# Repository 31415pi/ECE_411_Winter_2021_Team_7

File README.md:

# ECE411 Sunrise Alarm Clock - Team 7
,
> "Never wake-up in darkness..."

Actual project completion utilized a completely different set of hardware. Updates forthcoming. The Sunrise Alarm Clock is an add on board for an arduino which allows users to interact with an OLED display clock using guestures. The board features 12 RGB SMD LEDs which are used to display time in a meaningful way, indicate confirmation of guesture input, and provide an illuminated alarm experience. A buzzer along with two analog buttons are included to facilitate traditional inputs and alarms if necessary. 

View the [Product Design Specification](./Product%20Design%20Specification%20v1.pdf) for more information.

Look at the [Project Board](https://github.com/31415pi/ECE_411_Winter_2021_Team_7/projects/1).

Schematic located at [Hardware/Schematic](./Hardware/Schematic.pdf).

## Parts List

Parts list on [google drive](https://docs.google.com/spreadsheets/d/1yFu2dnekZCLbKxV9tUKsMTaaS4XpjHtpUTBXEi358RU/edit#gid=0). [Convert to Markdown](https://tabletomarkdown.com/convert-spreadsheet-to-markdown/).

| Part (datasheet link)                                                                                                                                  | Name                                                 | Type            | Notes                        | Datasheet                                                                                                                                                                                                                                                                                                  | Website                                                                                                    | Source                                                          | Price  |
| ------------------------------------------------------------------------------------------------------------------------------------------------------ | ---------------------------------------------------- | --------------- | ---------------------------- | ---------------------------------------------------------------------------------------------------------------------------------------------------------------------------------------------------------------------------------------------------------------------------------------------------------- | ---------------------------------------------------------------------------------------------------------- | --------------------------------------------------------------- | ------ |
| [HT16K33](https://github.com/31415pi/ECE_411_Winter_2021_Team_7/blob/main/Datasheets/HT16K33v120(LEDcontroller).pdf)                                   | RAM Mapping 16\*8 LED Controller Driver with keyscan | LED Controller  |                              |                                                                                                                                                                                                                                                                                                            | [https://www.holtek.com/productdetail/-/vg/16K33](https://www.holtek.com/productdetail/-/vg/16K33)         |                                                                 |        |
| [PIC18F26K42](https://github.com/31415pi/ECE_411_Winter_2021_Team_7/blob/main/Datasheets/PIC18(L)F26-27-45-46-47-55-56-57K42-Data-Sheet-40001919G.pdf) |                                                      | Microcontroller | Actual Model Read from Chip. | [https://www.microchip.com/content/dam/mchp/documents/MCU08/ProductDocuments/DataSheets/PIC18(L)F26-27-45-46-47-55-56-57K42-Data-Sheet-40001919G.pdf](https://www.microchip.com/content/dam/mchp/documents/MCU08/ProductDocuments/DataSheets/PIC18(L)F26-27-45-46-47-55-56-57K42-Data-Sheet-40001919G.pdf) | [https://www.microchip.com/en-us/product/PIC18F26K42](https://www.microchip.com/en-us/product/PIC18F26K42) | EPL                                                             | $ 1.50 |
| [IRM-05-5](https://github.com/31415pi/ECE_411_Winter_2021_Team_7/blob/main/Datasheets/IRM-05(ac-5vsupply).pdf)                                         |                                                      | DC Power Supply |                              |                                                                                                                                                                                                                                                                                                            |                                                                                                            | [Mouser](https://www.mouser.com/ProductDetail/709-IRM05-5)      | $ 8.81 |
| [MOC3052TVM](https://github.com/31415pi/ECE_411_Winter_2021_Team_7/blob/main/Datasheets/MOC3052M(ACcont).pdf)                                          |                                                      | AC Controller   |                              |                                                                                                                                                                                                                                                                                                            |                                                                                                            | [Mouser](https://www.mouser.com/ProductDetail/512-MOC3052SR2M)  | $ 1.15 |
| [ACST410-8BTR](https://github.com/31415pi/ECE_411_Winter_2021_Team_7/blob/main/Datasheets/ACST410(ACswitch).pdf)                                       |                                                      | AC Switch       |                              |                                                                                                                                                                                                                                                                                                            |                                                                                                            | [Mouser](https://www.mouser.com/ProductDetail/511-ACST410-8BTR) | $ 0.85 |
| [SFH628A](https://github.com/31415pi/ECE_411_Winter_2021_Team_7/blob/main/Datasheets/SFH628A(ACsensor).pdf)                                            |                                                      | AC Sensor       |                              |                                                                                                                                                                                                                                                                                                            |                                                                                                            | [Mouser](https://www.mouser.com/ProductDetail/782-SFH6286-4T)   | $ 1.27 |
| [COM-10931](https://github.com/31415pi/ECE_411_Winter_2021_Team_7/blob/main/Datasheets/COM-10931_ATA3492BW(7seg4digitSparkfun).pdf)                    | 7-Segment Display - 4-Digit (White)                  | Time Display    |                              | [http://cdn.sparkfun.com/datasheets/Components/LED/ATA3492BW\_2.pdf](http://cdn.sparkfun.com/datasheets/Components/LED/ATA3492BW_2.pdf)                                                                                                                                                                    | [https://www.sparkfun.com/products/10931](https://www.sparkfun.com/products/10931)                         | [Mouser](https://www.mouser.com/ProductDetail/474-COM-10931)    | $ 2.63 |

Alternate [Sparkfun Time Display](https://www.sparkfun.com/products/10931).

## Tools

- KiCad. [Third Party Libraries](https://www.kicad.org/libraries/third_party/)
- [Library Loader](https://componentsearchengine.com/tools) for loading schematics into KiCad and others. [Setup Instructions](https://www.samacsys.com/kicad/)

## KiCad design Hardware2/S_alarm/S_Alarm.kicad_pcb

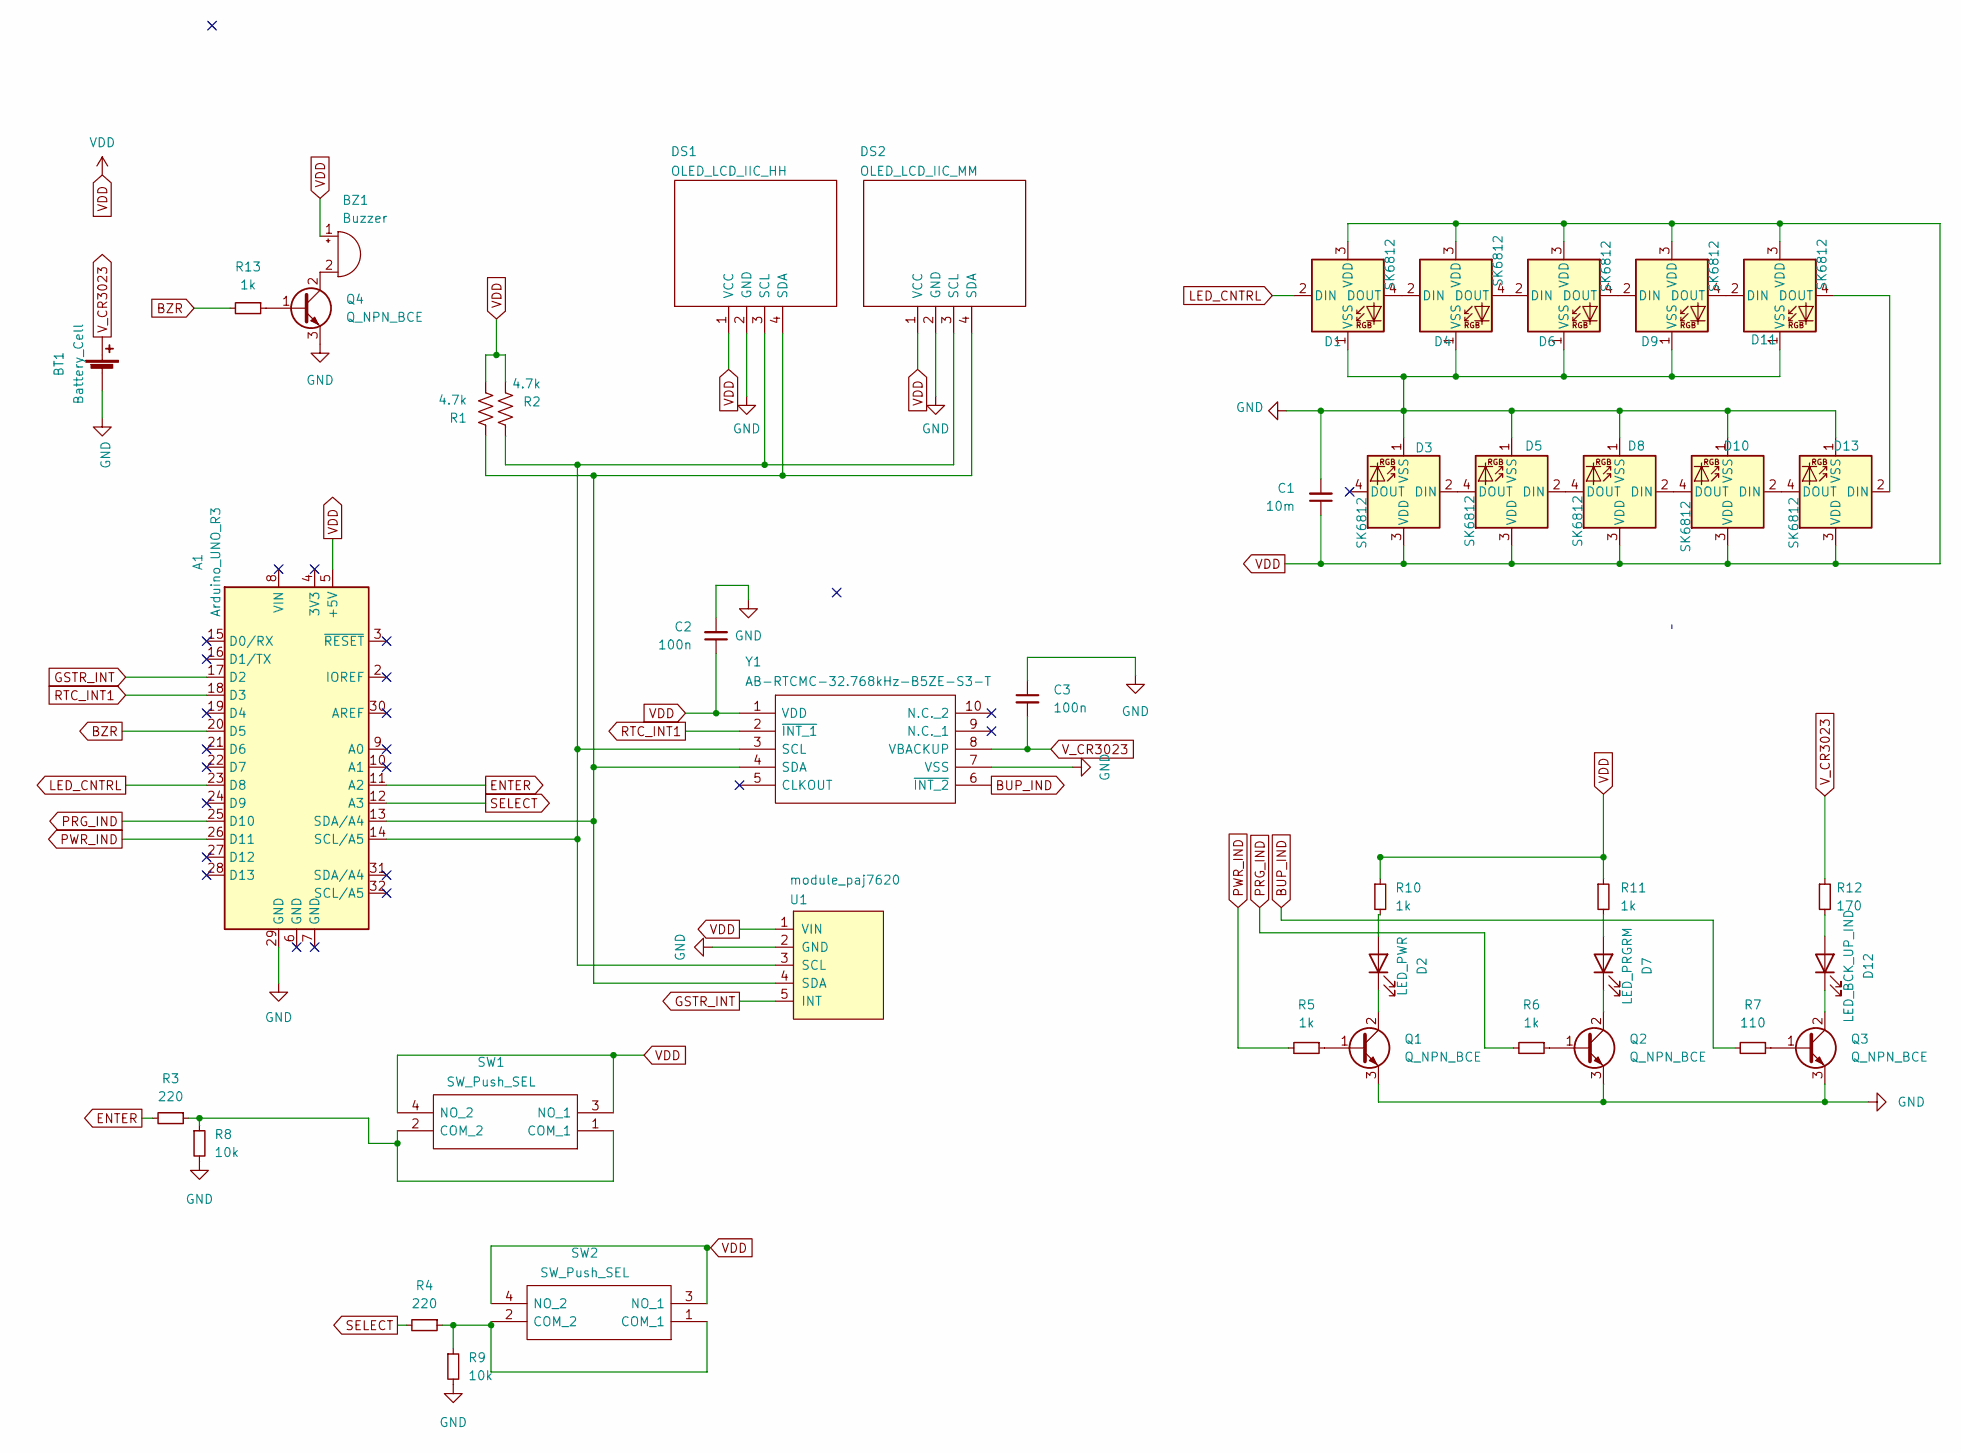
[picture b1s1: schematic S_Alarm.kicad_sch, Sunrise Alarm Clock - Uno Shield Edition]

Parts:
A1: Arduino_UNO_R3
BT1: Battery_Cell; BatteryHolder_MPD_BC2003_1x2032
BZ1: Buzzer; Buzzer_12x8.5RM6.5
C1: 10m; C_1206_3216Metric_Pad1.33x1.80mm_HandSolder
C2, C3: 100n; C_1206_3216Metric_Pad1.33x1.80mm_HandSolder
D1, D3, D4, D5, D6, D8, D9, D10, D11, D13: SK6812; LED_SK6812_PLCC4_5.0x5.0mm_P3.2mm
D2: LED_PWR; LED_1206_3216Metric_Pad1.42x1.75mm_HandSolder
D7: LED_PRGRM; LED_1206_3216Metric_Pad1.42x1.75mm_HandSolder
D12: LED_BCK_UP_IND; LED_1206_3216Metric_Pad1.42x1.75mm_HandSolder
DS1: OLED_LCD_IIC_HH; Display_OLED_128x64_0.96
DS2: OLED_LCD_IIC_MM; Display_OLED_128x64_0.96
Q1, Q2, Q3, Q4: Q_NPN_BCE; SOT-23_Handsoldering
R1, R2: 4.7k; R_1206_3216Metric_Pad1.30x1.75mm_HandSolder
R3, R4: 220; R_1206_3216Metric_Pad1.30x1.75mm_HandSolder
R5, R6, R10, R11, R13: 1k; R_1206_3216Metric_Pad1.30x1.75mm_HandSolder
R7: 110; R_1206_3216Metric_Pad1.30x1.75mm_HandSolder
R8, R9: 10k; R_1206_3216Metric_Pad1.30x1.75mm_HandSolder
R12: 170; R_1206_3216Metric_Pad1.30x1.75mm_HandSolder
SW1, SW2: SW_Push_SEL; PTS526SK15SMTR2LFS; Mouser Part Number 611-PTS526SK15SMR2L
U1: module_paj7620
Y1: AB-RTCMC-32.768kHz-B5ZE-S3-T; ABRTCMC32768kHzB5ZES3T; Manufacturer_Part_Number AB-RTCMC-32.768kHz-B5ZE-S3-T; Mouser Part Number 815-ABMC-327B5ZES3T

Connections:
BUP_IND: R7.2, Y1.6 (~INT_2)
BZR: A1.20 (D5), R13.2
ENTER: A1.11 (A2), R3.2
GND: A1.29 (GND), BT1.2 (-), C1.2, C2.2, C3.1, D1.1 (VSS), D3.1 (VSS), D4.1 (VSS), D5.1 (VSS), D6.1 (VSS), D8.1 (VSS), D9.1 (VSS), D10.1 (VSS), D11.1 (VSS), D13.1 (VSS), DS1.2 (GND), DS2.2 (GND), Q1.3 (E), Q2.3 (E), Q3.3 (E), Q4.3 (E), R8.2, R9.2, U1.2 (GND), Y1.7 (VSS)
GSTR_INT: A1.17 (D2), U1.5 (INT)
LED_CNTRL: A1.23 (D8), D1.2 (DIN)
unnamed: A1.13 (SDA/A4), DS1.4 (SDA), DS2.4 (SDA), R1.1, U1.4 (SDA), Y1.4 (SDA)
unnamed: A1.14 (SCL/A5), DS1.3 (SCL), DS2.3 (SCL), R2.1, U1.3 (SCL), Y1.3 (SCL)
unnamed: BZ1.2 (+), Q4.2 (C)
unnamed: D1.4 (DOUT), D4.2 (DIN)
unnamed: D2.1 (K), Q1.2 (C)
unnamed: D2.2 (A), R10.2
unnamed: D3.2 (DIN), D5.4 (DOUT)
unnamed: D4.4 (DOUT), D6.2 (DIN)
unnamed: D5.2 (DIN), D8.4 (DOUT)
unnamed: D6.4 (DOUT), D9.2 (DIN)
unnamed: D7.1 (K), Q2.2 (C)
unnamed: D7.2 (A), R11.2
unnamed: D10.2 (DIN), D13.4 (DOUT)
unnamed: D8.2 (DIN), D10.4 (DOUT)
unnamed: D9.4 (DOUT), D11.2 (DIN)
unnamed: D11.4 (DOUT), D13.2 (DIN)
unnamed: D12.1 (K), Q3.2 (C)
unnamed: D12.2 (A), R12.2
unnamed: Q1.1 (B), R5.1
unnamed: Q2.1 (B), R6.1
unnamed: Q3.1 (B), R7.1
unnamed: Q4.1 (B), R13.1
unnamed: R3.1, R8.1, SW1.1 (COM_1), SW1.2 (COM_2)
unnamed: R4.1, R9.1, SW2.1 (COM_1), SW2.2 (COM_2)
PRG_IND: A1.25 (D10), R6.2
PWR_IND: A1.26 (D11), R5.2
RTC_INT1: A1.18 (D3), Y1.2 (~INT_1)
SELECT: A1.12 (A3), R4.2
VDD: A1.5 (+5V), BZ1.1 (-), C1.1, C2.1, D1.3 (VDD), D3.3 (VDD), D4.3 (VDD), D5.3 (VDD), D6.3 (VDD), D8.3 (VDD), D9.3 (VDD), D10.3 (VDD), D11.3 (VDD), D13.3 (VDD), DS1.1 (VCC), DS2.1 (VCC), R1.2, R2.2, R10.1, R11.1, SW1.3 (NO_1), SW1.4 (NO_2), SW2.3 (NO_1), SW2.4 (NO_2), U1.1 (VIN), Y1.1 (VDD)
V_CR3023: BT1.1 (+), C3.2, R12.1, Y1.8 (VBACKUP)

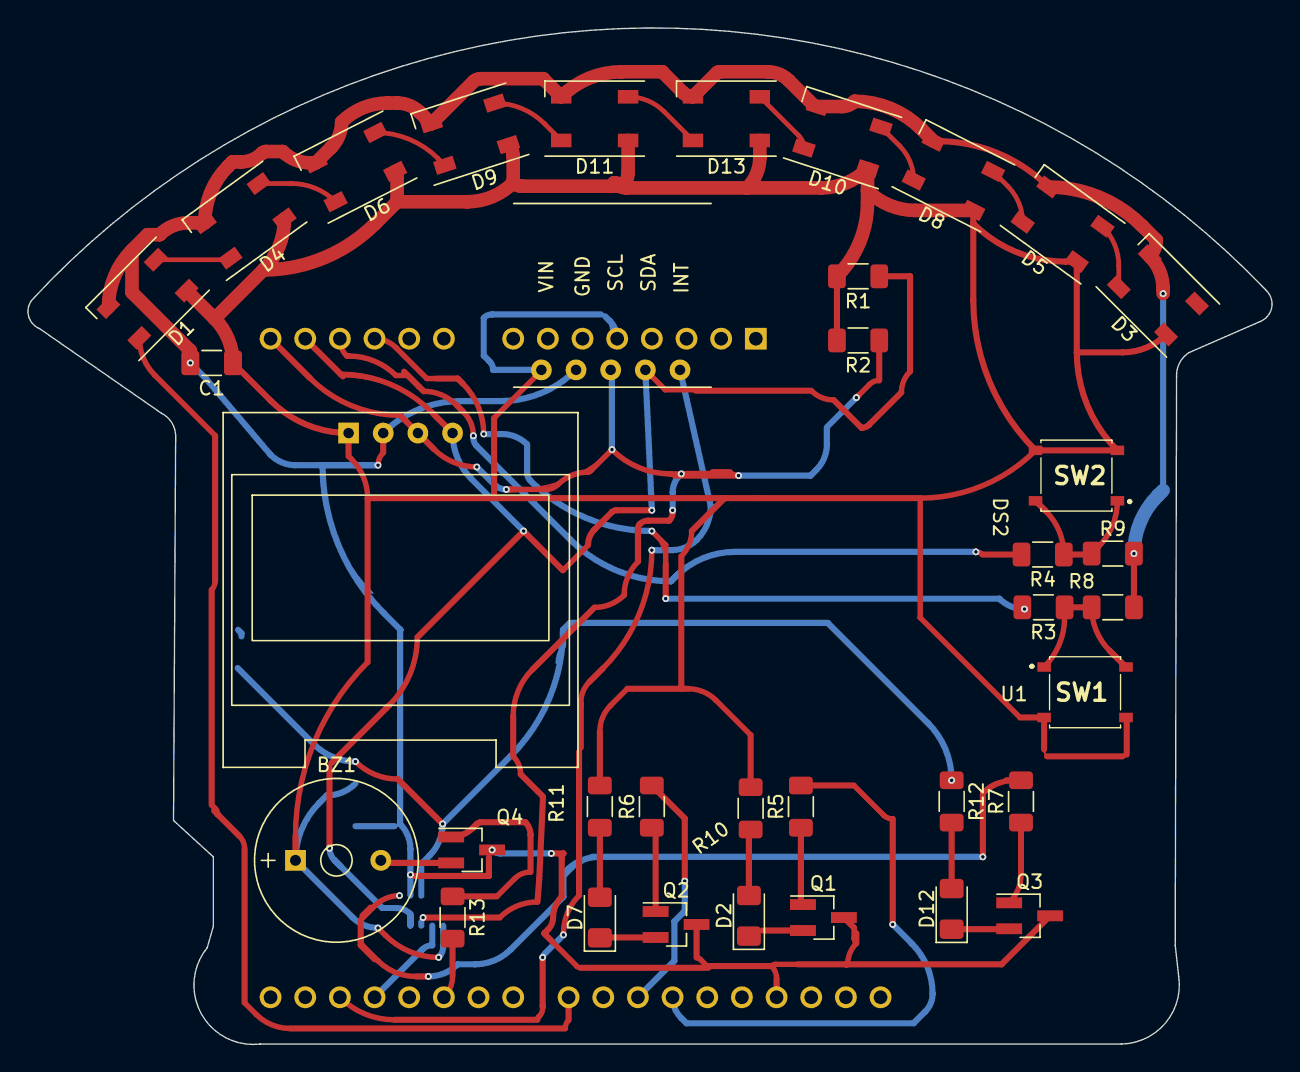
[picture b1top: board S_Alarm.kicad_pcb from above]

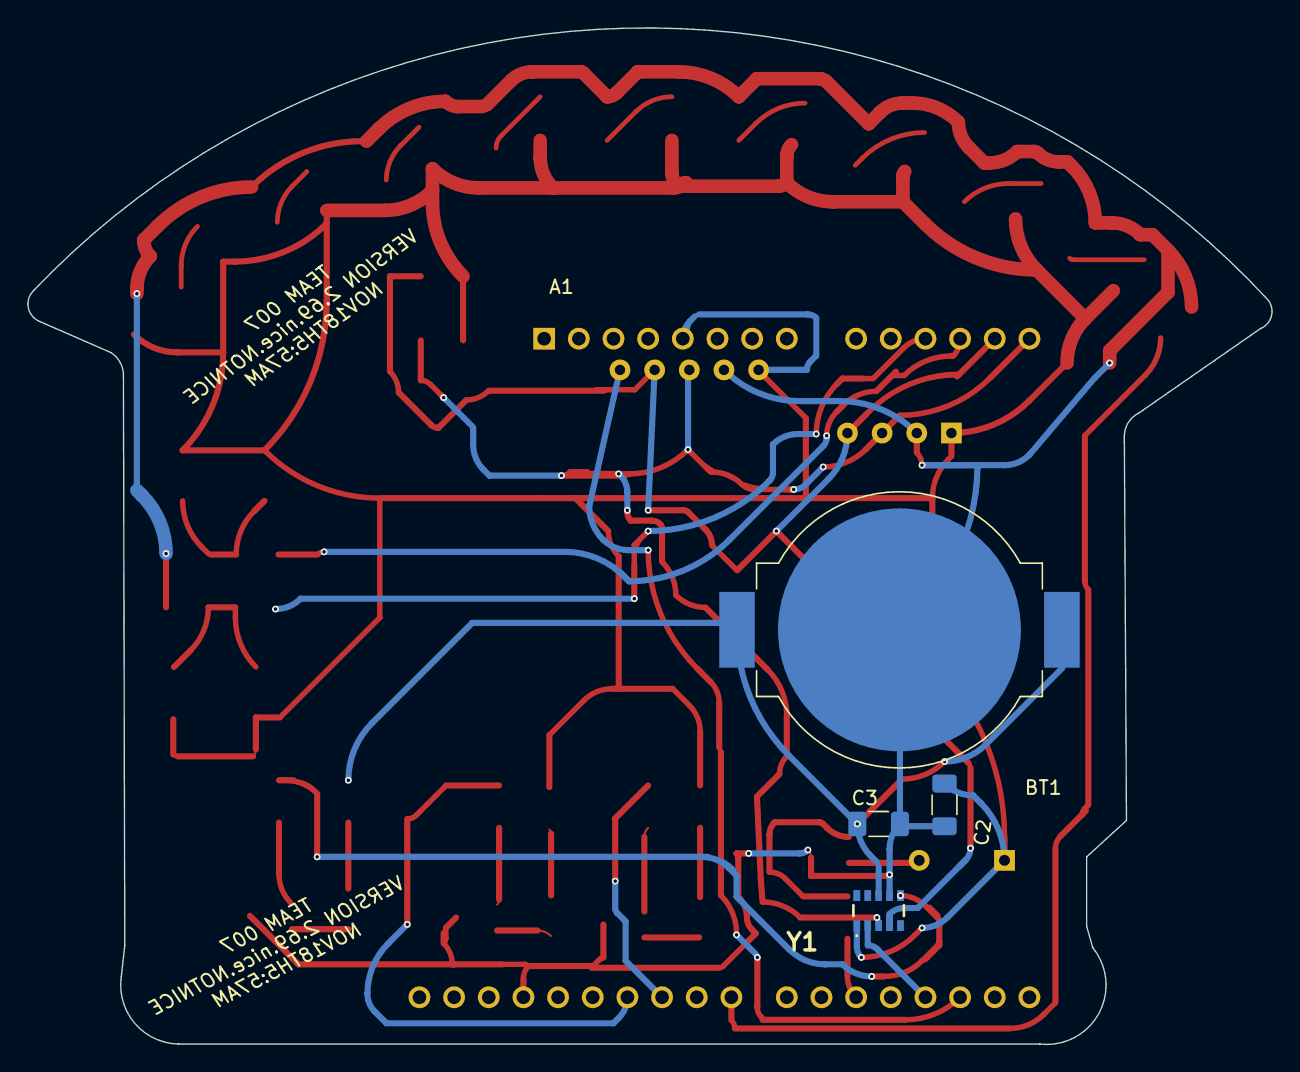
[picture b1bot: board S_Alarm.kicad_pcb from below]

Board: 2 copper layers, 91.2 x 74.5 mm, 41 parts (5 on the bottom side), 36 nets.

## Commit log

2021-10-20 Create PDS.md
    PDS skeleton
2021-10-20 Update PDS.md
    format
2021-10-21 Add Product Specification
2021-10-21 Added datasheets, readme
2021-10-21 Fix link in readme. use '%20' for space in url.
2021-10-21 Update PDS with page numbers
2021-10-22 Add project board link to readme
2021-10-24 Create test.rtf
    pushing a teswt commit
2021-10-24 Create log.txt
    Beginning tests
2021-10-24 Create Production Ready Guesture control.c
    TEST
2021-10-24 removing tests
    removing tests
2021-10-27 Added parts and datasheets
2021-10-27 Added PIC datasheets
2021-10-28 Schematic v0.1 got AC circuit started.
2021-10-28 Add buzzer datasheet.
2021-10-28 Added status report
2021-10-29 Updated schematic, reset button, labeled lines
2021-10-29 Added MPLABX project
    Configured processor registers. Enabled Low Voltage Programing (LVP). Need initial program first.
    Added simple blink code for an LED.
2021-10-29 Added .gitignore and 7seg datasheet
2021-11-03 Add PIC data sheets, Planning Template
2021-11-04 Schematic: Added programing header
2021-11-04 Schematic: Next Version. Added datasheets
2021-11-04 Remove v5 Schematic. Add LED datasheets.
2021-11-04 Remove v5 Schematic. Add correct LED datasheets.
2021-11-04 Schematic Updates
    Changed to 3.3v supply to accommodate gesture sensor.
    Added gesture sensor.
    Added test led.
2021-11-04 Schematic: Updated. Fixes
    Added Gesture Sensor.
    Switch to 3.3v supply. Modified resistors.
    Fix test LED.
    Added datasheet.
2021-11-04 Moved schematic to Firmware. Added link in Readme.
2021-11-04 fw: update MC to PIC18F26K42
    Noticed that was the version listed on the controller. They seem to be
    compatible.
2021-11-05 fw: blink program working. Programed with PICkit4
    Makefile-genesis.properties does not need to be version controlled.
    https://www.microchip.com/forums/m716169.aspx
2021-11-05 fw: Reduced programmer voltage to 3.3v for testing
2021-11-05 fw: Fix version control. Add header.
    Which files to version control?
    https://electronics.stackexchange.com/questions/131588/which-files-to-version-control-in-mplabx-nbproject-directory
2021-11-05 doc: Clean up datasheets
    Removed for K22 processor. Added for K42.
    Added tool datasheets.
    Change naming. Try to have less spaces for easier linking.
2021-11-05 hw: Added library parts for LED controller, readme
2021-11-05 doc: Updated readmes, parts list source on docs.
2021-11-05 hw: Schematic v4. Pin Assignments
    Schematic for LED Display.
    *Noticed LED Display needs 5v!*
    Add PIN assignments.
    Added PIN assignments for gesture sensor.
    Moved Schematic to hardware folder.
2021-11-08 hw: Added Complete schematic v0.5 + datasheets
    - Updated 5v to 3.3v Power Supply.
    - Updated Logic control for LED Display.
    Use single decoder with V_IH = 1.5v. Works for 1-way control.
    - Added a third digit line for alarm and colon.
    - Finished buzzer circuit. Tested prototype.
    - Corrected Zero Crossing Circuit to be on power line always.
2021-11-08 fw: Added AC controller code for UNO
2021-11-08 hw: Adding layout of AC controller.
2021-11-11 Updated Schematic Buttons, Connector, Ran ERC
    - Added buttons.
    - Added AC to Main board connection. Split power lines.
    - Corrected non-connected.
    - Updated schematic symbols.
    - Ran annotations. Components now have numbers.
    - Ran ERC check.
2021-11-11 Added some missing datasheets.
2021-11-11 Added generated parts list.
2021-11-11 Replaced generic button.
2021-11-11 Added Bill of Materials.
2021-12-03 Removed old AC code from Firmware.
2021-12-03 fw: Added Arduino code for gesture sensor
2021-12-05 fw: Updated gesture and interaction code
    Update state machine for gesture and interaction code.
2021-12-06 Create SomeTesting.txt
    Testing the neopixel shield version
2021-12-08 fw: Working Clock Display.
    Alarm function, Clock function, adjust function working.
    Alarm is visual only.
    Display library custom to use less memory. Close to running out of memory.
2021-12-08 Create RTC Code
2021-12-09 fw: Added Gradual Bringup Code.
2021-12-09 fw: Ready For Demo
2021-12-09 fw: Corrected time for demo.
2021-12-09 fw: Corrected alarm toggle on/off during glow.
2021-12-09 fw: Added light on/off gestures.
2021-12-10 fw: Added morning light.
2021-12-10 hw: Added board files from Maddie, schematic printout, mods, docs
    Added missing docs.
2021-12-10 Create LICENSE
    Add license based on past discussions with the team.
2022-08-13 Update README.md
    Added intro reflecting design change
